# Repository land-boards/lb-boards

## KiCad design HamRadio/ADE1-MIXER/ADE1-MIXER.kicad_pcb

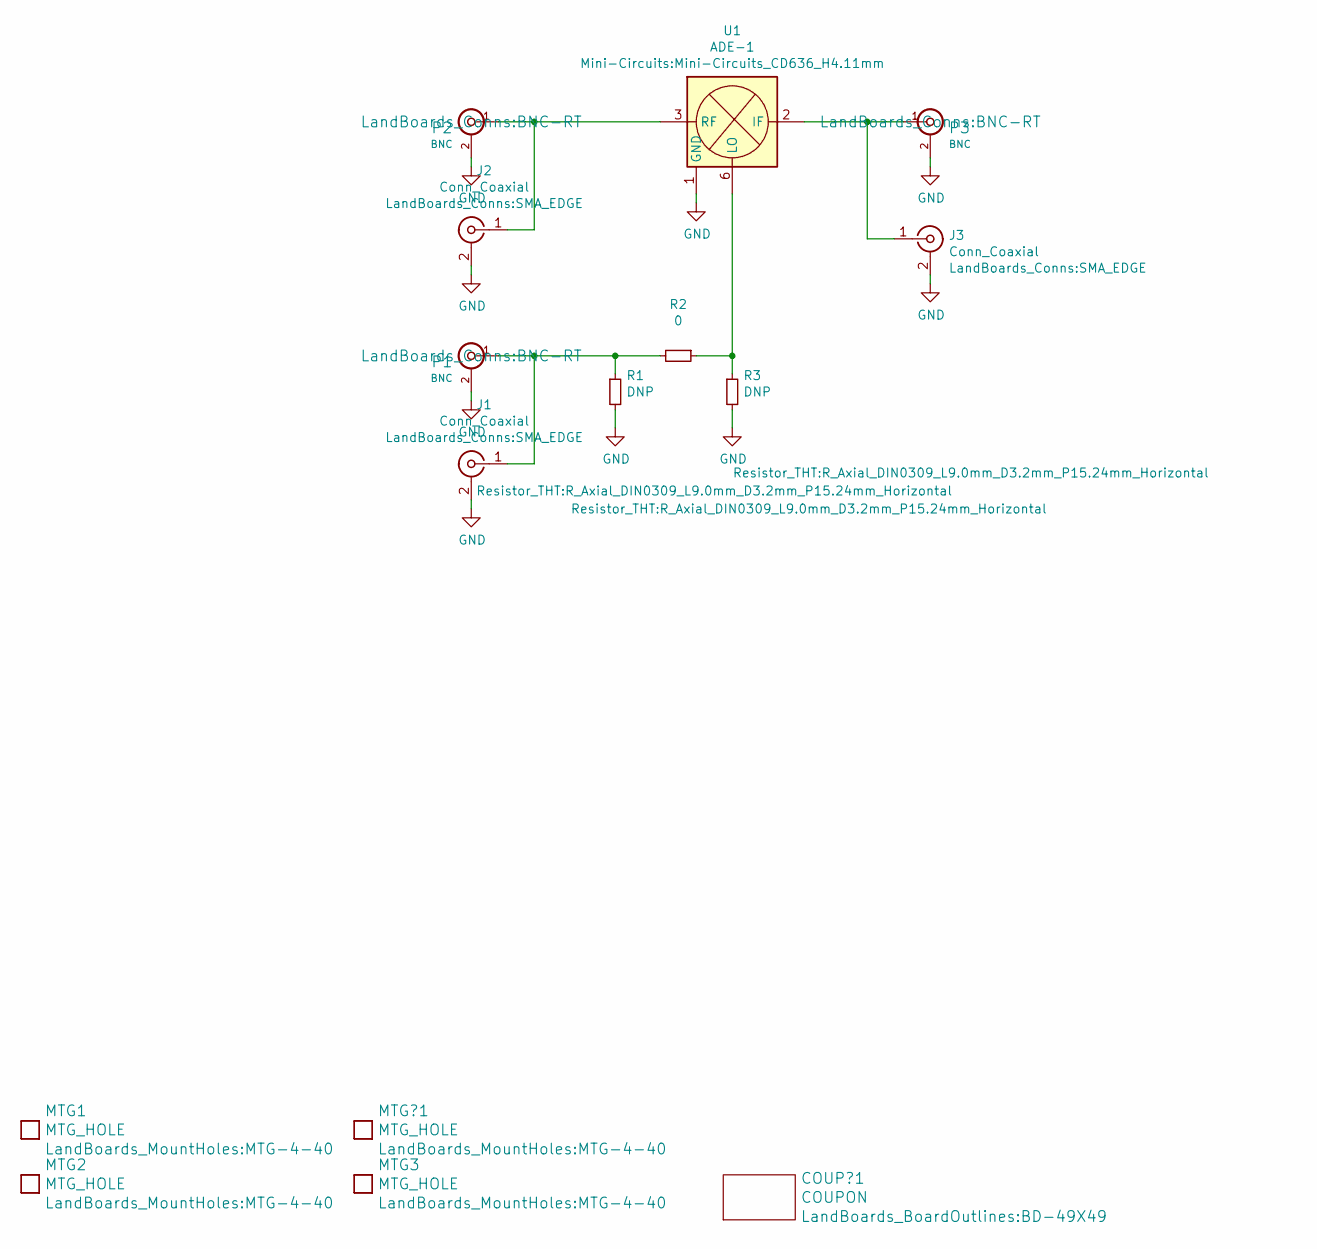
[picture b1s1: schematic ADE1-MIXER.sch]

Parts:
COUP?1: COUPON; BD-49X49
J1, J2, J3: Conn_Coaxial; SMA_EDGE
MTG1, MTG2, MTG3: MTG_HOLE; MTG-4-40
MTG?1: MTG_HOLE; MTG-4-40
P1, P2, P3: BNC; BNC-RT
R1, R3: DNP; R_Axial_DIN0309_L9.0mm_D3.2mm_P15.24mm_Horizontal
R2: 0; R_Axial_DIN0309_L9.0mm_D3.2mm_P15.24mm_Horizontal
U1: ADE-1; Mini-Circuits_CD636_H4.11mm

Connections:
GND: J1.2 (Ext), J2.2 (Ext), J3.2 (Ext), P1.2 (Ext), P2.2 (Ext), P3.2 (Ext), R1.2, R3.2, U1.1 (GND), U1.4 (GND), U1.5 (GND)
unnamed: J1.1 (In), P1.1 (In), R1.1, R2.2
unnamed: J2.1 (In), P2.1 (In), U1.3 (RF)
unnamed: J3.1 (In), P3.1 (In), U1.2 (IF)
unnamed: R2.1, R3.1, U1.6 (LO)

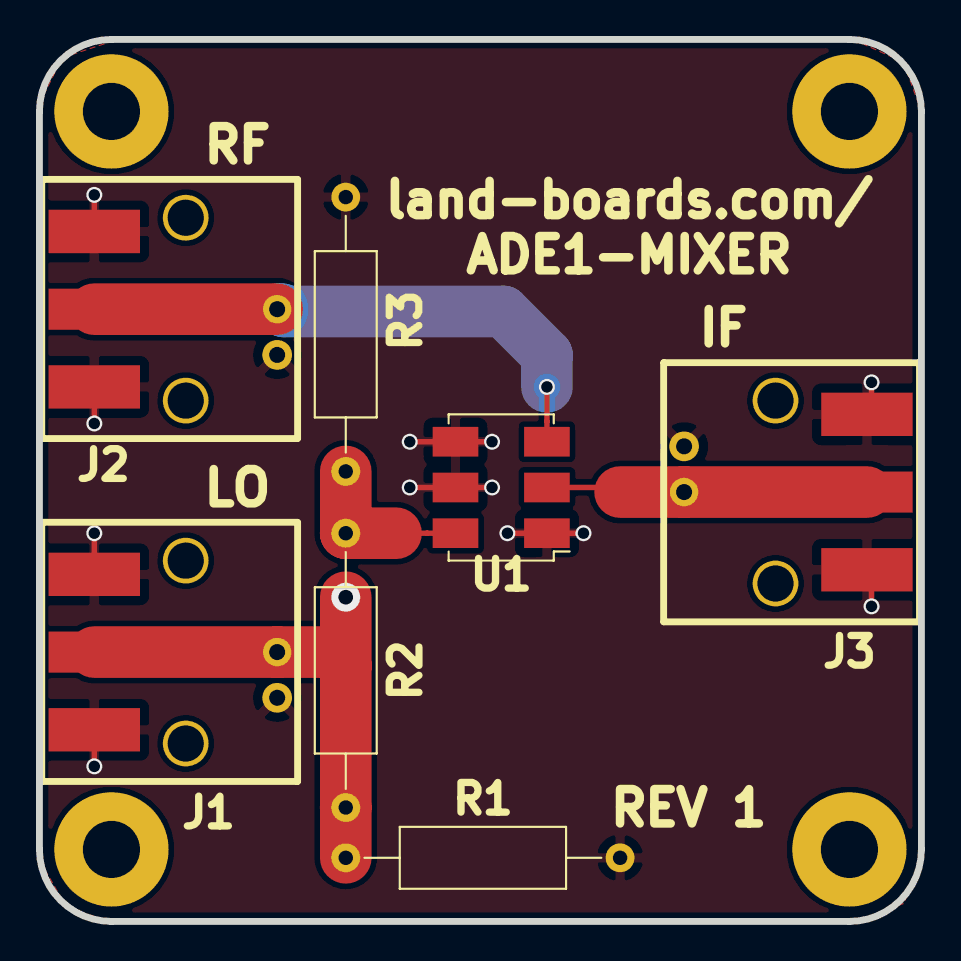
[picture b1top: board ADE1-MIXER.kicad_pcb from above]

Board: 2 copper layers, 49.0 x 49.0 mm, 14 parts (0 on the bottom side), 5 nets.

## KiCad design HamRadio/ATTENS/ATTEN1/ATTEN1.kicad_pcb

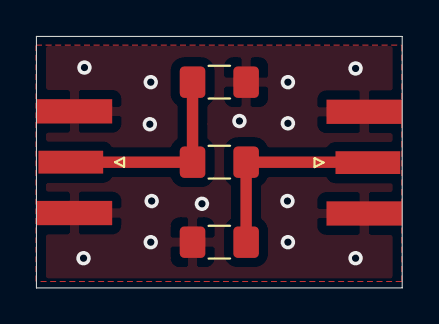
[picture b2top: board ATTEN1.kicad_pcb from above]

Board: 2 copper layers, 20.3 x 14.0 mm, 5 parts (0 on the bottom side), 3 nets.

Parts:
P1, P6: SMA; SMA_Samtec_SMA-J-P-H-ST-EM1_EdgeMount
R1, R2, R3: R_Small; R_1206_3216Metric_Pad1.42x1.75mm_HandSolder

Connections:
/G03: P1.2, P6.2, R1.2, R3.2
unnamed: P1.1, R1.1, R2.2
unnamed: P6.1, R2.1, R3.1

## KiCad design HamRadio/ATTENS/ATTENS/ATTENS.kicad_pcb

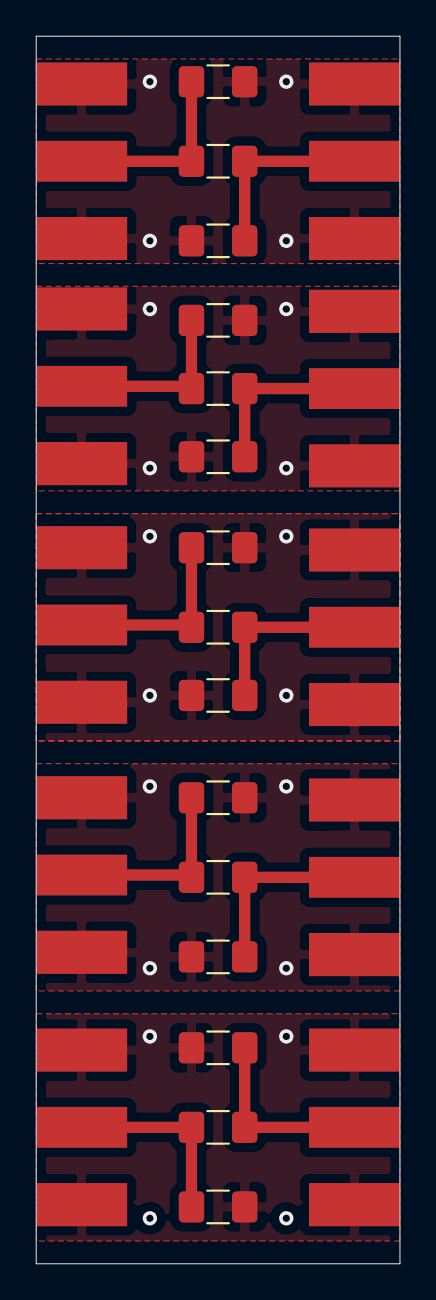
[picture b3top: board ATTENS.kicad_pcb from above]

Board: 2 copper layers, 20.3 x 68.6 mm, 25 parts (0 on the bottom side), 15 nets.

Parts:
P1, P2, P3, P4, P5, P6, P7, P8, P9, P10: SMA; SMA_EDGE
R1, R2, R3, R4, R5, R6, R7, R8, R9, R10, R11, R12, R13, R14, R15: R_Small; R_1206_3216Metric_Pad1.42x1.75mm_HandSolder

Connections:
/G03: P1.2, P6.2, R1.2, R11.2
/G10: P2.2, P7.2, R2.2, R12.2
/G20: P3.2, P8.2, R3.2, R13.2
/G30: P4.2, P9.2, R4.2, R14.2
/G40: P5.2, P10.2, R5.2, R15.2
unnamed: P1.1, R1.1, R6.2
unnamed: P2.1, R2.1, R7.2
unnamed: P3.1, R3.1, R8.2
unnamed: P4.1, R4.1, R9.2
unnamed: P5.1, R5.1, R10.2
unnamed: P6.1, R6.1, R11.1
unnamed: P7.1, R7.1, R12.1
unnamed: P8.1, R8.1, R13.1
unnamed: P9.1, R9.1, R14.1
unnamed: P10.1, R10.1, R15.1

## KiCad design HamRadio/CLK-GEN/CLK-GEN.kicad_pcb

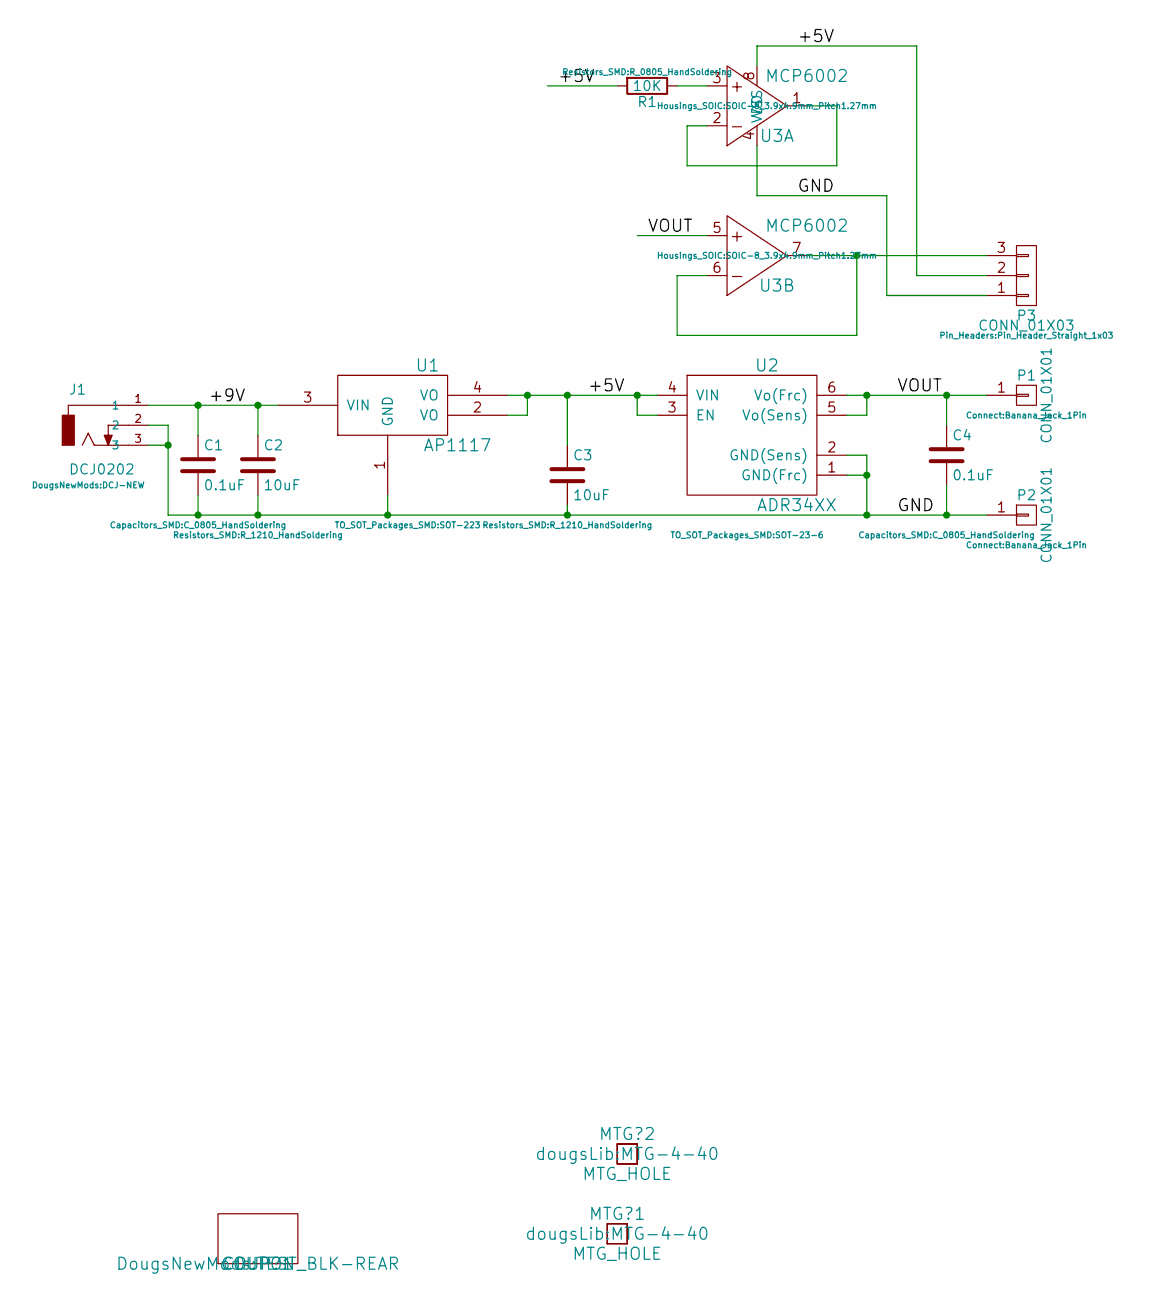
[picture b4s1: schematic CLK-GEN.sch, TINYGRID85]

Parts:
C1, C4: 0.1uF; C_0805_HandSoldering
C2, C3: 10uF; R_1210_HandSoldering
COUP?1: COUPON; TEST_BLK-REAR
J1: DCJ0202; DCJ-NEW
MTG?1, MTG?2: MTG_HOLE; MTG-4-40
P1, P2: CONN_01X01; Banana_Jack_1Pin
P3: CONN_01X03; Pin_Header_Straight_1x03
R1: 10K; R_0805_HandSoldering
U1: AP1117; SOT-223
U2: ADR34XX; SOT-23-6
U3: MCP6002; SOIC-8_3.9x4.9mm_Pitch1.27mm

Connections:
/+5V: C3.1, P3.2, R1.2, U1.2 (VO), U1.4 (VO), U2.3 (EN), U2.4 (VIN), U3.8 (VDD)
/+9V: C1.1, C2.1, J1.1, U1.3 (VIN)
/GND: C1.2, C2.2, C3.2, C4.2, J1.2, J1.3, P2.1, P3.1, U1.1 (GND), U2.1 (GND(Frc)), U2.2 (GND(Sens)), U3.4 (VSS)
/VOUT: C4.1, P1.1, U2.5 (Vo(Sens)), U2.6 (Vo(Frc)), U3.5 (+)
unnamed: P3.3, U3.6 (-), U3.7 (Q)
unnamed: R1.1, U3.3 (+)
unnamed: U3.1 (Q), U3.2 (-)

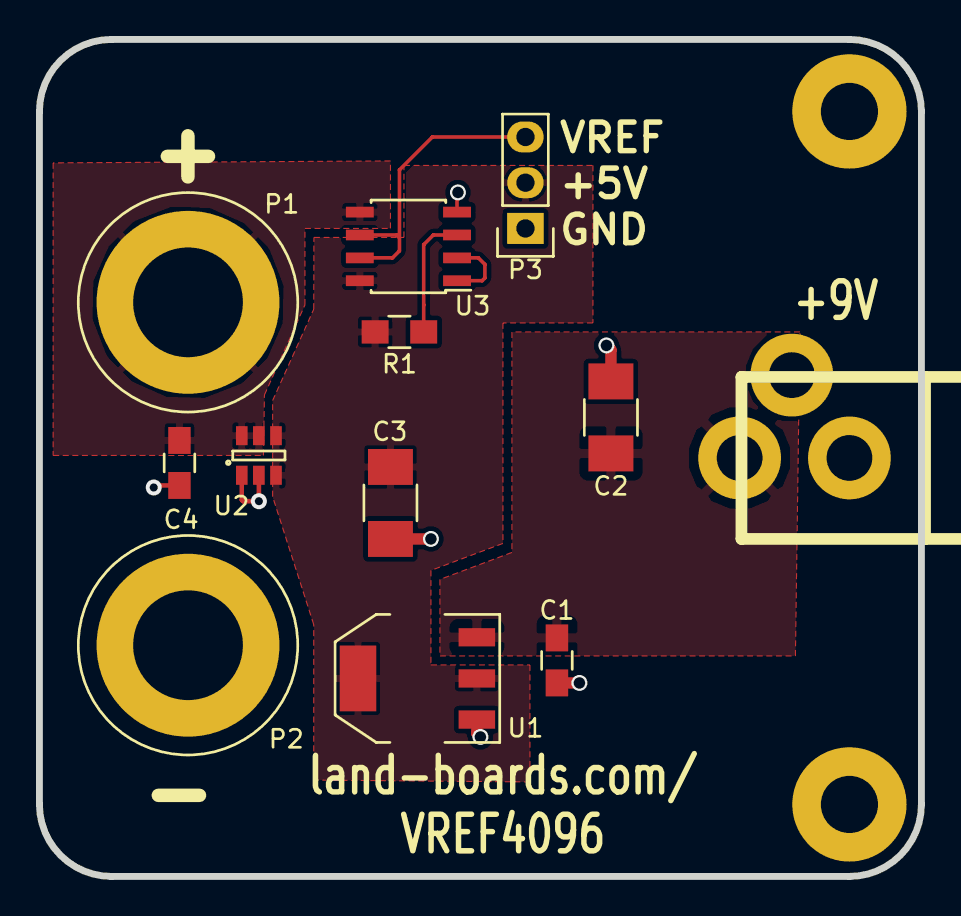
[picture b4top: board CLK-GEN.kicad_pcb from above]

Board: 2 copper layers, 49.0 x 46.5 mm, 15 parts (0 on the bottom side), 7 nets.

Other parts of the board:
TEST: COUPON; TEST_BLK-REAR

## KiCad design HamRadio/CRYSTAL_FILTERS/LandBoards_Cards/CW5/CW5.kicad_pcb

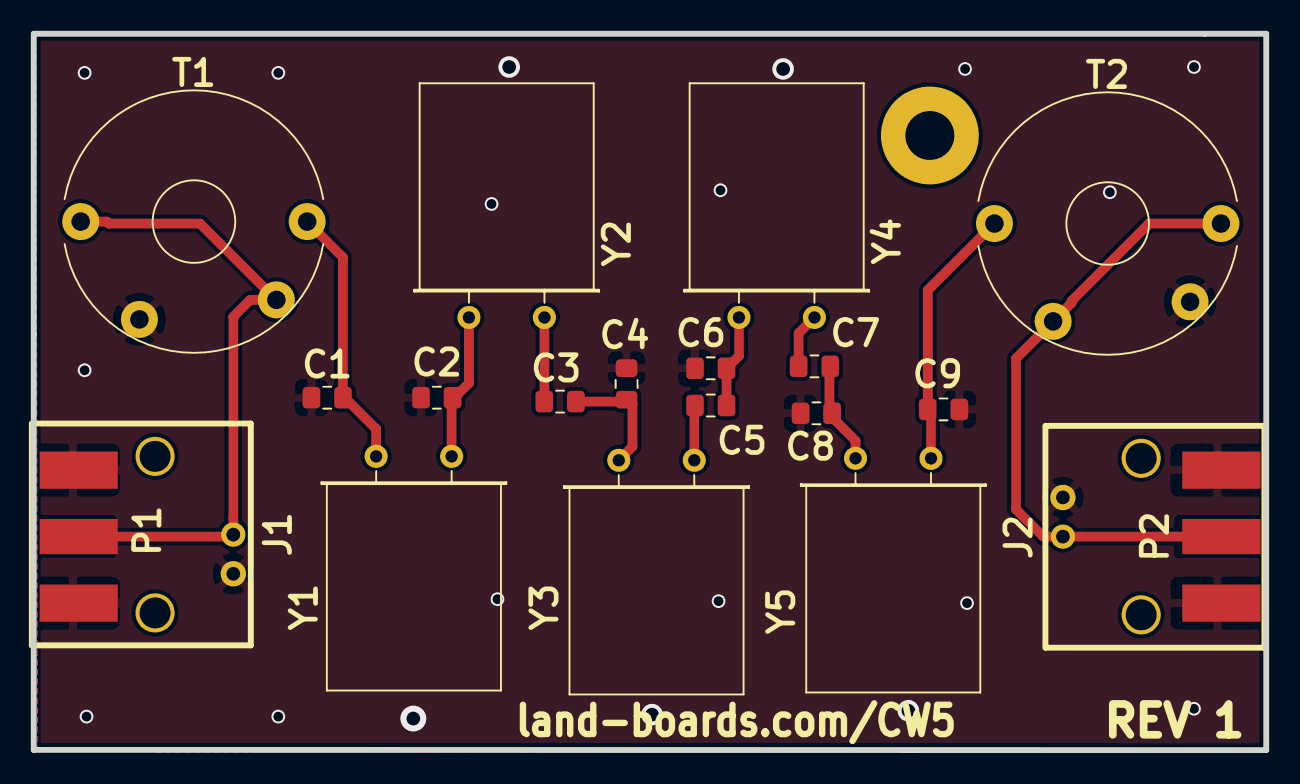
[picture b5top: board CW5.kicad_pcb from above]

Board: 2 copper layers, 80.0 x 46.5 mm, 22 parts (0 on the bottom side), 12 nets.

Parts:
C1, C9: 100pF; C_0805_2012Metric_Pad1.15x1.40mm_HandSolder
C2, C8: 330; C_0805_2012Metric_Pad1.15x1.40mm_HandSolder
C3, C7: 270; C_0805_2012Metric_Pad1.15x1.40mm_HandSolder
C4, C6: 680; C_0805_2012Metric_Pad1.15x1.40mm_HandSolder
C5: 200; C_0805_2012Metric_Pad1.15x1.40mm_HandSolder
J1, J2: BNC; BNC-RT
MTG4: MTG_HOLE; MTG-4-40
P1, P2: BNC; SMA_EDGE
T1, T2: Transformer_1P_1S; L_Toroid_Horizontal_4pIN
TESTED: COUPON; TEST_BLK-REAR
Y1, Y2, Y3, Y4, Y5: 9.000; Crystal_HC49-U_Horizontal

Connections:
GND: C1.2, C2.2, C4.2, C6.1, C8.2, C9.2, J1.2, J2.2, P1.2, P2.2, T1.2, T2.3
unnamed: C1.1, T1.4, Y1.1
unnamed: C2.1, Y1.2, Y2.2
unnamed: C3.1, Y2.1
unnamed: C3.2, C4.1, Y3.1
unnamed: C5.1, Y3.2
unnamed: C5.2, C6.2, Y4.2
unnamed: C7.1, Y4.1
unnamed: C7.2, C8.1, Y5.1
unnamed: C9.1, T2.1, Y5.2
unnamed: J1.1, P1.1, T1.1, T1.3
unnamed: J2.1, P2.1, T2.2, T2.4
